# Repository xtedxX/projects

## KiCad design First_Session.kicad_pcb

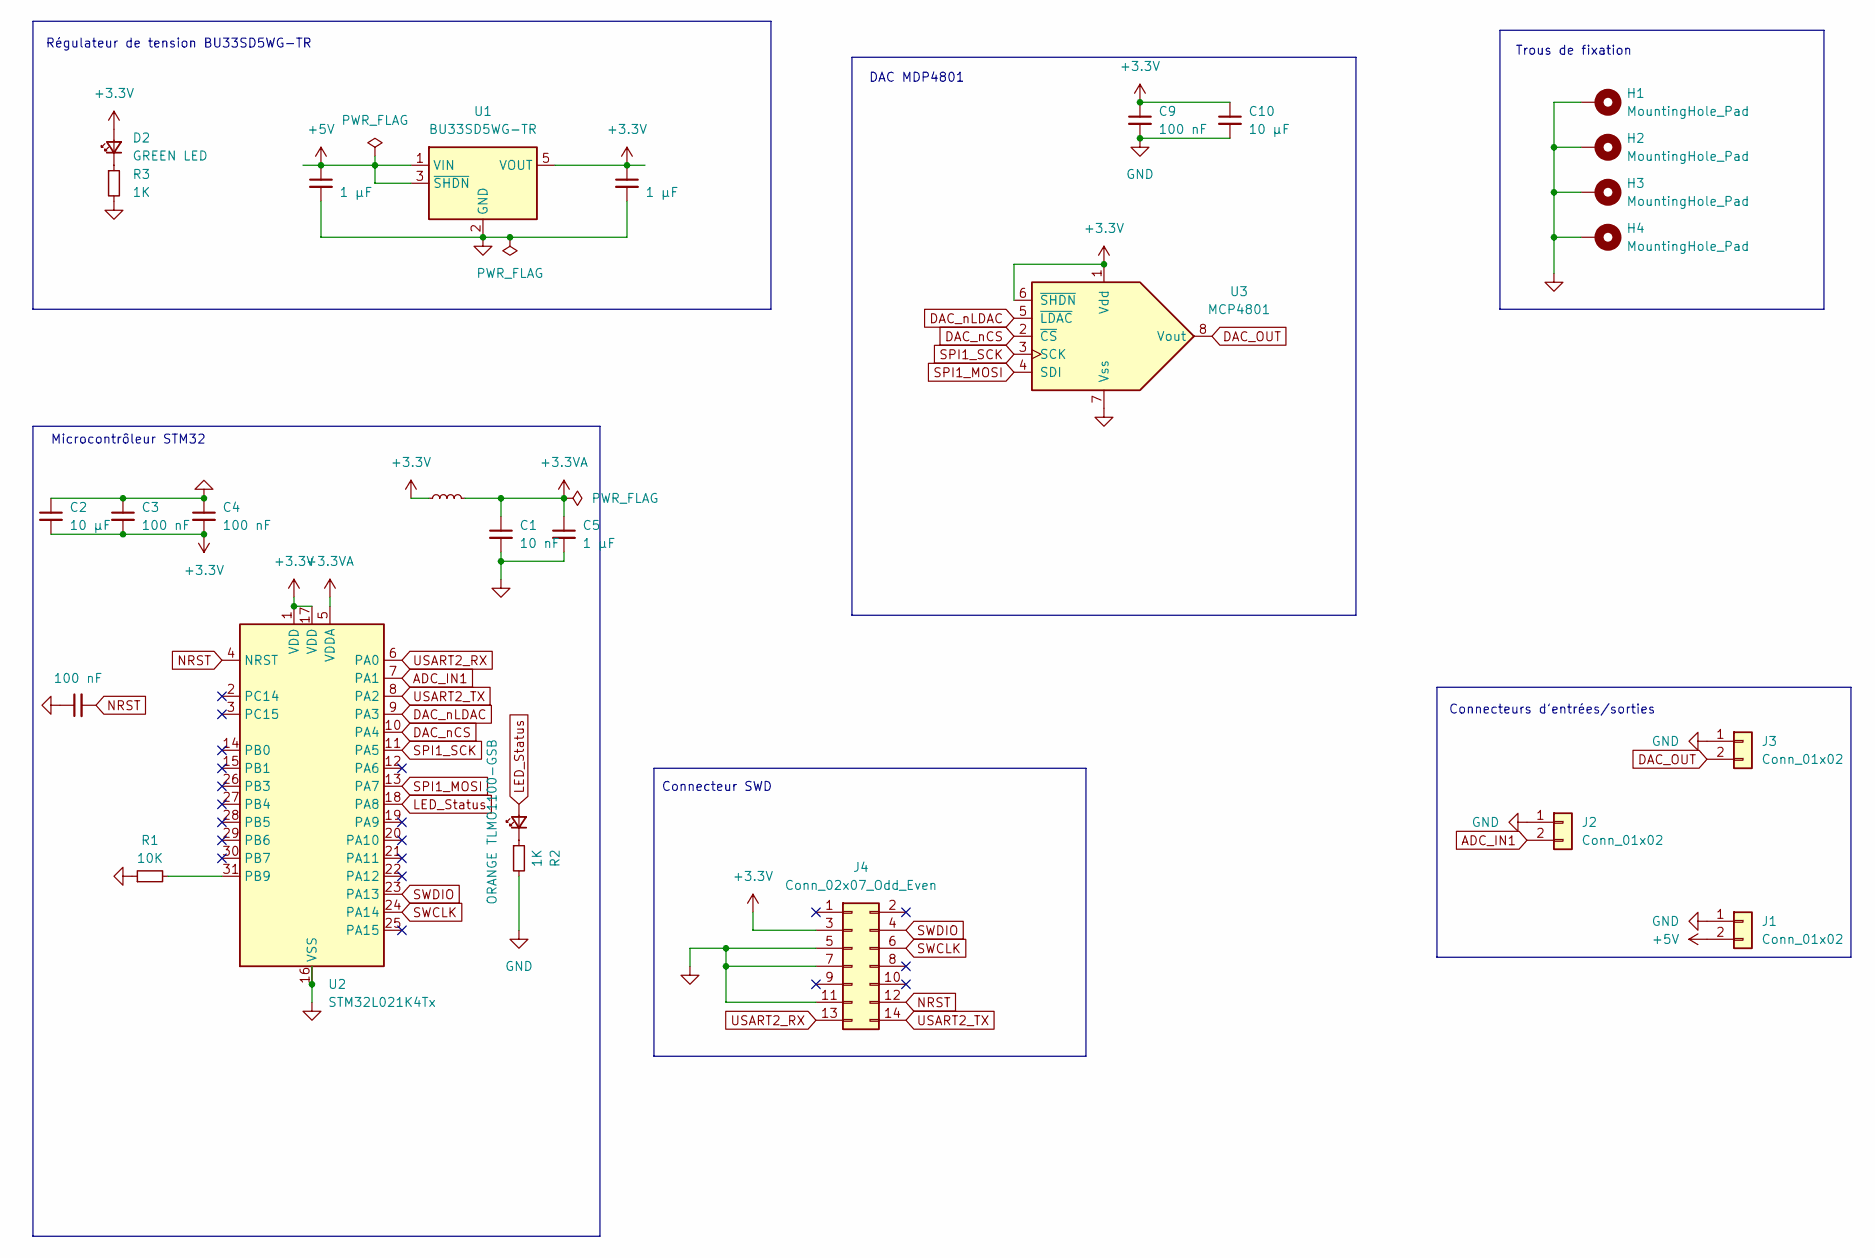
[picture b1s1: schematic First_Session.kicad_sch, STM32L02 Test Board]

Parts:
C1: 10 nF; C_0603_1608Metric_Pad1.08x0.95mm_HandSolder
C2, C10: 10 µF; C_0603_1608Metric_Pad1.08x0.95mm_HandSolder
C3, C4, C6, C9: 100 nF; C_0603_1608Metric_Pad1.08x0.95mm_HandSolder
C5, C7, C8: 1 µF; C_0603_1608Metric_Pad1.08x0.95mm_HandSolder
D1: ORANGE TLMO1100-GSB; LED_0603_1608Metric_Pad1.05x0.95mm_HandSolder
D2: GREEN LED; LED_0603_1608Metric_Pad1.05x0.95mm_HandSolder
H1, H2, H3, H4: MountingHole_Pad; MountingHole_3.2mm_M3_DIN965_Pad
J1, J2, J3: Conn_01x02; JST_XH_B2B-XH-A_1x02_P2.50mm_Vertical
J4: Conn_02x07_Odd_Even; PinHeader_2x07_P1.27mm_Vertical_SMD
L1: 39 nH; L_0805_2012Metric_Pad1.05x1.20mm_HandSolder
R1: 10K; R_0603_1608Metric_Pad0.98x0.95mm_HandSolder
R2, R3: 1K; R_0603_1608Metric_Pad0.98x0.95mm_HandSolder
U1: BU33SD5WG-TR; SOT-23-5
U2: STM32L021K4Tx; LQFP-32_7x7mm_P0.8mm
U3: MCP4801; SOIC-8_3.9x4.9mm_P1.27mm

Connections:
+3.3V: C2.2, C3.2, C4.2, C8.1, C9.1, C10.1, D2.2 (A), J4.3, L1.1, U1.5 (VOUT), U2.1 (VDD), U2.17 (VDD), U3.1 (Vdd), U3.6 (~SHDN)
+3.3VA: C1.1, C5.1, L1.2, U2.5 (VDDA)
+5V: C7.1, J1.2, U1.1 (VIN), U1.3 (~SHDN)
ADC_IN1: J2.2, U2.7 (PA1)
DAC_OUT: J3.2, U3.8 (Vout)
DAC_nCS: U2.10 (PA4), U3.2 (~CS)
DAC_nLDAC: U2.9 (PA3), U3.5 (~LDAC)
GND: C1.2, C2.1, C3.1, C4.1, C5.2, C6.1, C7.2, C8.2, C9.2, C10.2, H1.1, H2.1, H3.1, H4.1, J1.1, J2.1, J3.1, J4.5, J4.7, J4.11, R1.1, R2.2, R3.2, U1.2 (GND), U2.16 (VSS), U2.32 (VSS), U3.7 (Vss)
LED_Status: D1.2 (A), U2.18 (PA8)
NRST: C6.2, J4.12, U2.4 (NRST)
unnamed: D1.1 (K), R2.1
unnamed: D2.1 (K), R3.1
unnamed: R1.2, U2.31 (PB9)
SPI1_MOSI: U2.13 (PA7), U3.4 (SDI)
SPI1_SCK: U2.11 (PA5), U3.3 (SCK)
SWCLK: J4.6, U2.24 (PA14)
SWDIO: J4.4, U2.23 (PA13)
USART2_RX: J4.13, U2.6 (PA0)
USART2_TX: J4.14, U2.8 (PA2)

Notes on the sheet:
Connecteur SWD
Trous de fixation
DAC MDP4801
Microcontrôleur STM32
Connecteurs d'entrées/sorties
Régulateur de tension BU33SD5WG-TR

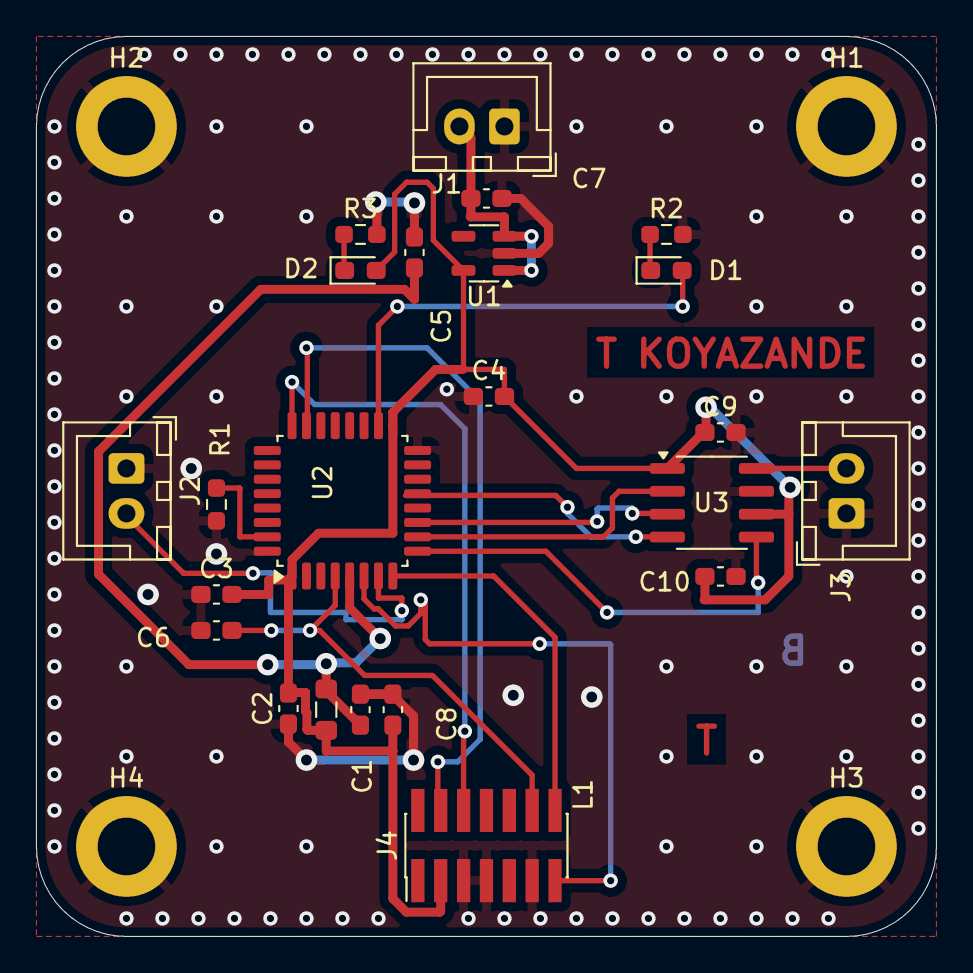
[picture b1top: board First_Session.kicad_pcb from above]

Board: 2 copper layers, 50.0 x 50.0 mm, 27 parts (0 on the bottom side), 19 nets.
